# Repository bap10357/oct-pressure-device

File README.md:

THIS REPOSITORY HAS BEEN MOVED TO CODEBERG --> https://codeberg.org/brpe/au-oct-pressure-device/

The source code, schematics, and documentation for the optical coherence tomography air pressure control device for the Asia University Biodesign Lab (https://pweb.asia.edu.tw/cwlung/).

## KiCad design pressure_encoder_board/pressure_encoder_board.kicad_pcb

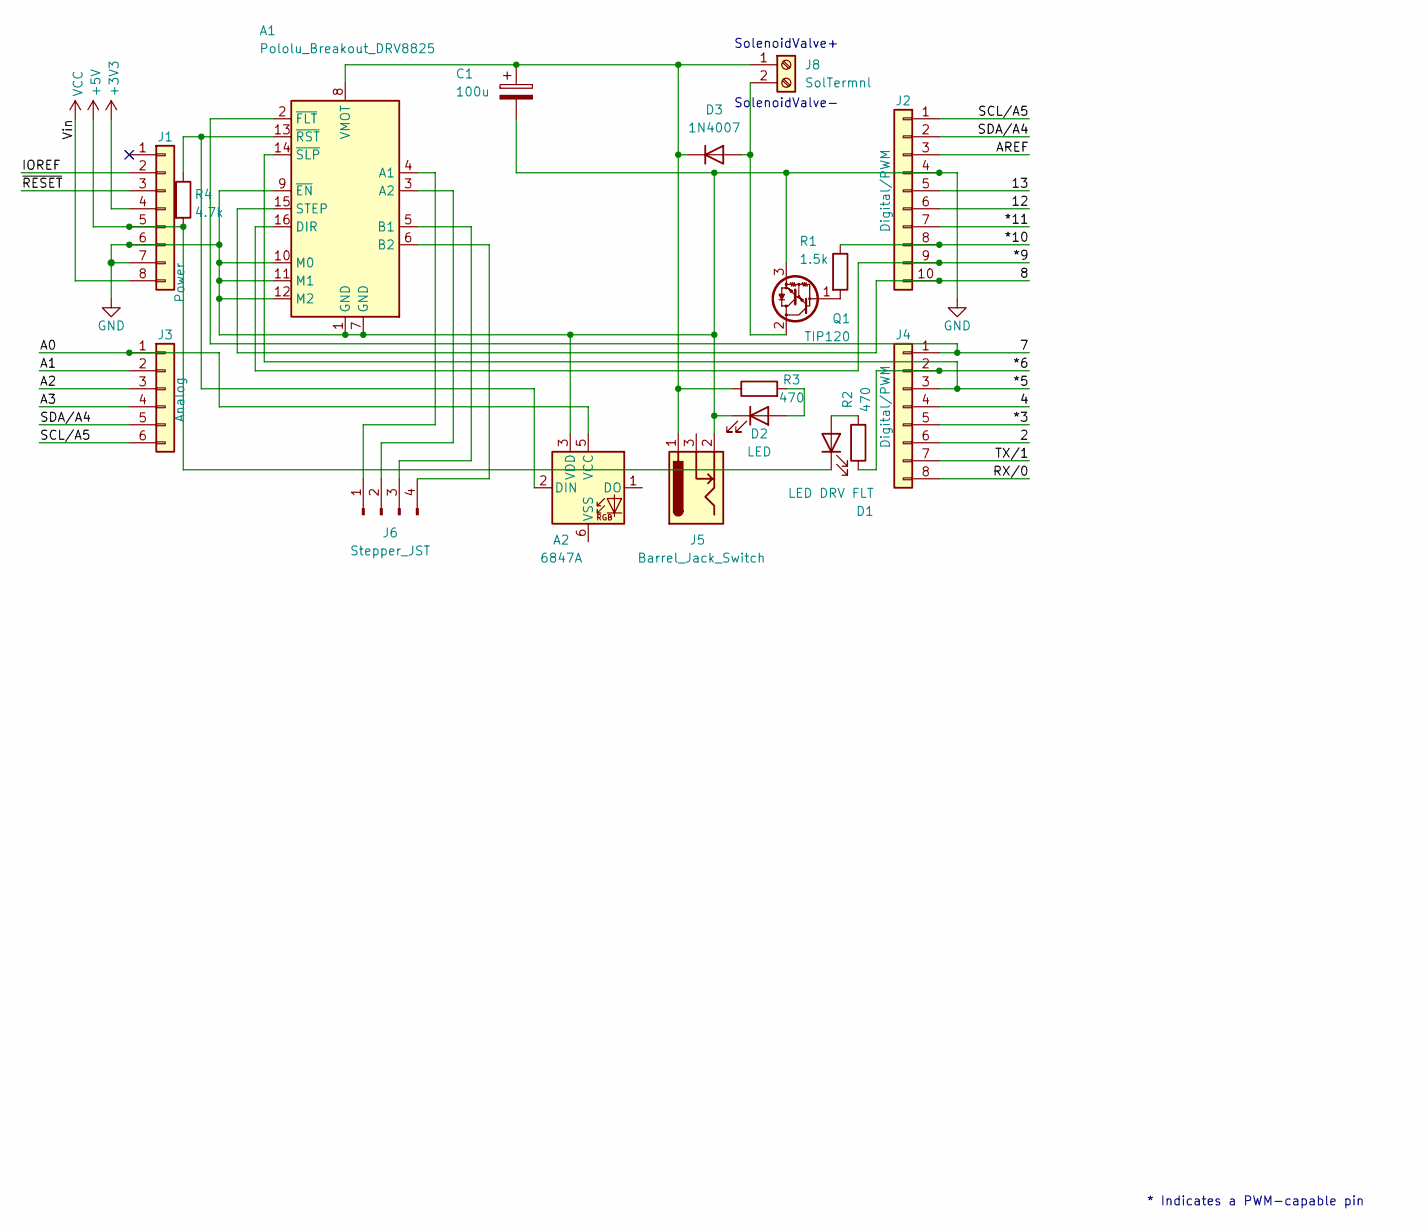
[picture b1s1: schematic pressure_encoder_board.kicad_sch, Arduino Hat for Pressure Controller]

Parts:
A1: Pololu_Breakout_DRV8825; Pololu_Breakout-16_15.2x20.3mm
A2: 6847A; DIP-6_W10.16mm
C1: 100u; CP_Radial_D6.3mm_P2.50mm
D1: LED DRV FLT; LED_D5.0mm
D2: LED; LED_D5.0mm
D3: 1N4007; D_DO-41_SOD81_P10.16mm_Horizontal
J1: Power; PinHeader_1x08_P2.54mm_Vertical
J2: Digital/PWM; PinHeader_1x10_P2.54mm_Vertical
J3: Analog; PinHeader_1x06_P2.54mm_Vertical
J4: Digital/PWM; PinHeader_1x08_P2.54mm_Vertical_Flipped_Trimmed
J5: Barrel_Jack_Switch; BarrelJack_Horizontal_Trimmed
J6: Stepper_JST; JST_PH_S4B-PH-K_1x04_P2.00mm_Horizontal
J8: SolTermnl; TerminalBlock_Phoenix_PT-1,5-2-5.0-H_1x02_P5.00mm_Horizontal
Q1: TIP120; TO-220-3_Vertical
R1: 1.5k; R_Axial_DIN0207_L6.3mm_D2.5mm_P10.16mm_Horizontal
R2, R3: 470; R_Axial_DIN0207_L6.3mm_D2.5mm_P10.16mm_Horizontal
R4: 4.7k; R_Axial_DIN0207_L6.3mm_D2.5mm_P10.16mm_Horizontal

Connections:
+3V3: J1.4
+5V: D1.1 (K), J1.5, R4.2
/2: J4.6
/4: J4.4
/7: A1.2 (~FLT), J4.1
/8: A1.15 (STEP), J2.10
/12: J2.6
/13: J2.5
/*3: J4.5
/*5: A1.14 (~SLP), J4.3
/*6: J4.2, R2.1
/*9: A1.16 (DIR), J2.9
/*10: J2.8, R1.1
/*11: J2.7
/A0: A2.5 (VCC), J3.1
/A1: J3.2
/A2: J3.3
/A3: J3.4
/AREF: J2.3
/IOREF: J1.2
/RX/0: J4.8
/SCL/A5: J2.1, J3.6
/SDA/A4: J2.2, J3.5
/TX/1: J4.7
/~RESET: J1.3
GND: A1.1 (GND), A1.7 (GND), A1.9 (~EN), A1.10 (M0), A1.11 (M1), A1.12 (M2), A2.3 (VDD), C1.2, D2.1 (K), J1.6, J1.7, J2.4, J5.2, Q1.3 (E)
unnamed: A1.4 (A1), J6.1
unnamed: A1.3 (A2), J6.2
unnamed: A1.5 (B1), J6.3
unnamed: A1.6 (B2), J6.4
unnamed: A1.8 (VMOT), C1.1, D3.1 (K), J5.1, J8.1, R3.1
unnamed: A1.13 (~RST), A2.2 (DIN), R4.1
unnamed: D1.2 (A), R2.2
unnamed: D2.2 (A), R3.2
unnamed: D3.2 (A), J8.2, Q1.2 (C)
unnamed: Q1.1 (B), R1.2
VCC: J1.8

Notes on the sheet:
SolenoidValve-
* Indicates a PWM-capable pin
SolenoidValve+

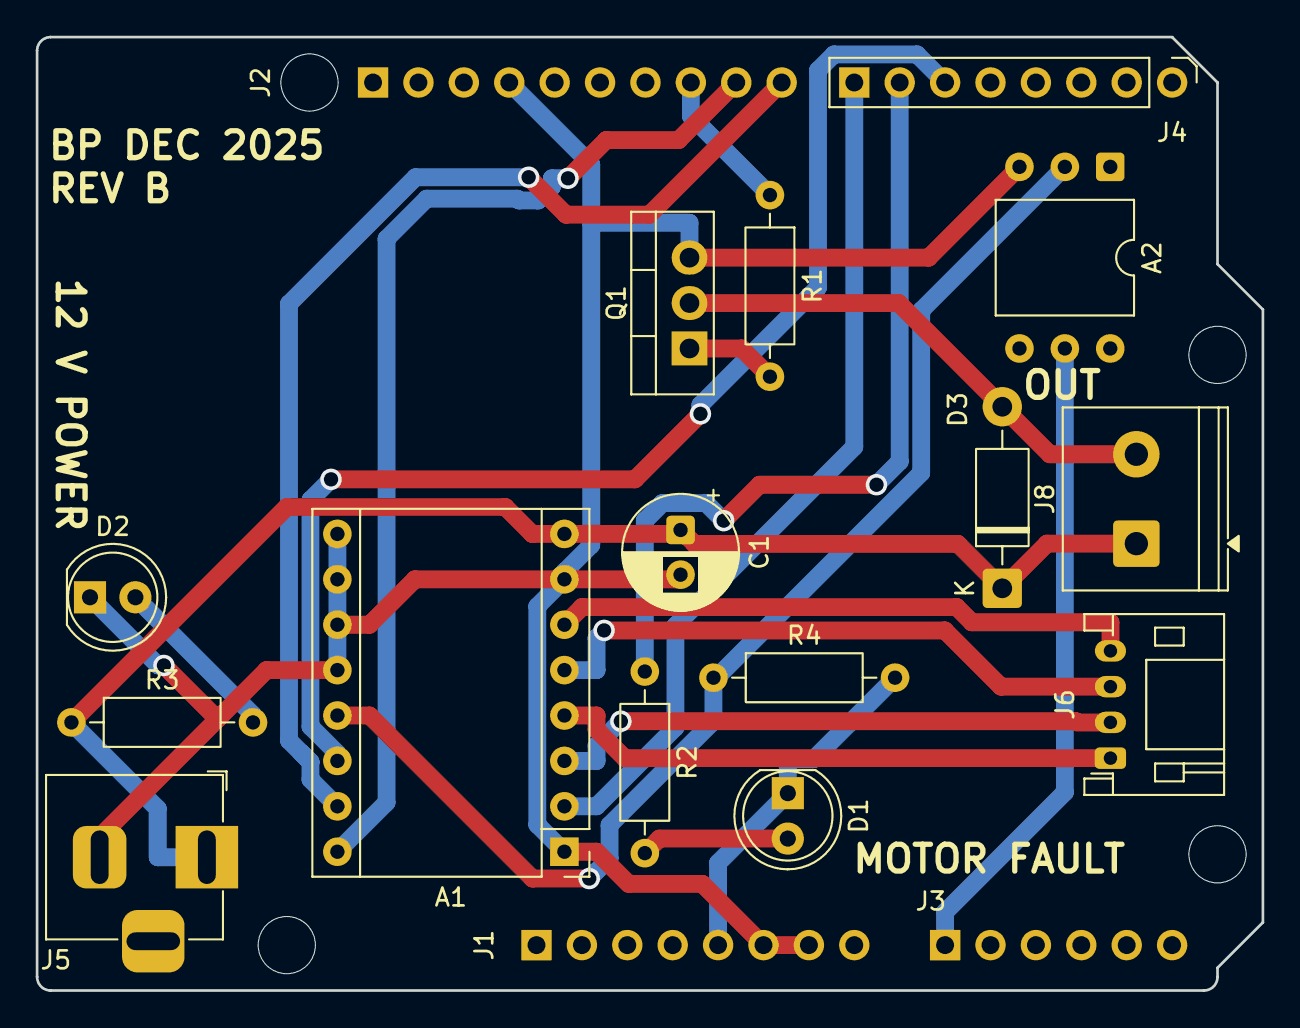
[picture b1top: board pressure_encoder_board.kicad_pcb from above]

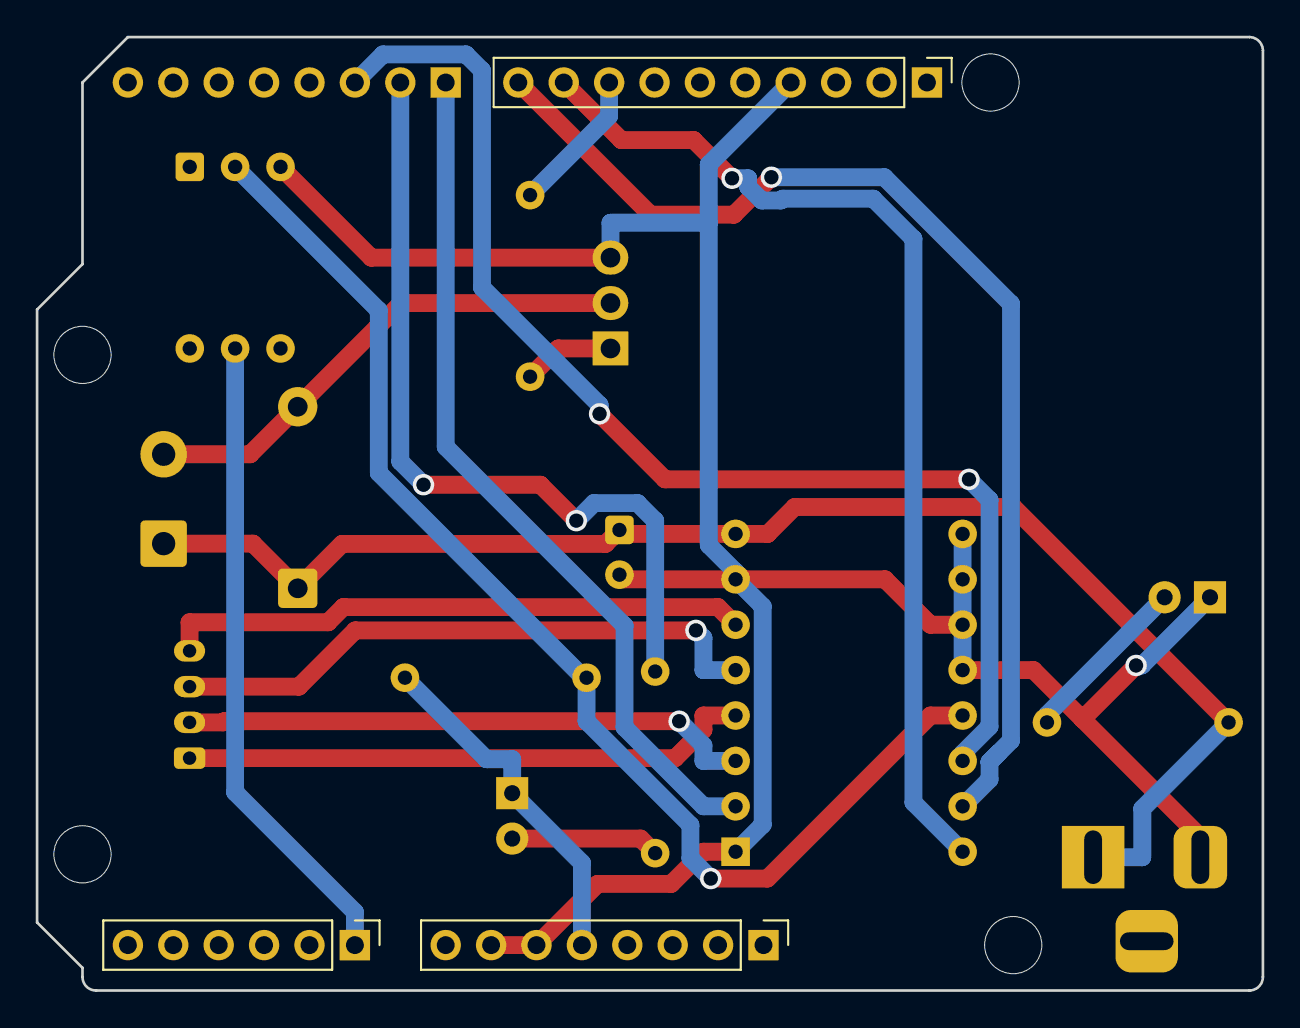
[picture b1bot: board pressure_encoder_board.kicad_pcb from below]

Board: 2 copper layers, 68.6 x 53.3 mm, 22 parts (4 on the bottom side), 21 nets.

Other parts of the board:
MH1, MH2, MH3, MH4: MountingHole_3.2mm

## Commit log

2025-12-28 Change reference to /calibration.csv -> /sys/calibration.csv at end of calibration process
2025-12-28 Add documentation to Git repository
2025-12-28 Update figure file names
2025-12-28 Update project summary document
2025-12-29 Remove ._ files
2025-12-29 Remove ._ files and update documentation
2025-12-30 Add note about manual valve reset
2025-12-30 Add YouTube instructional video links
2025-12-30 Change YouTube txt to HTML
2025-12-30 Add YouTube link HTML
2025-12-30 Change YouTube link HTML to MD and add
2025-12-30 Update YouTube link MD formatting
2025-12-30 Fixed CW3 -> PW3
2026-01-01 Fix 11 -> 1 Hz typo in pilot study, change purchase -> manufacturing company for valves
2026-01-01 Reformat manual documents
2026-01-05 Add BOM to pressure device report
2026-01-05 Updated Bill of Materials for APCD and LPC
2026-03-13 Remove LPC documentation
2026-03-13 Remove excess file from documentation
2026-05-26 Update pressure_encoder.ino
    Fix program record times not aligning with program run times
